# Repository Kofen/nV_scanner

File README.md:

# Nv scanner

FW is at best a hack

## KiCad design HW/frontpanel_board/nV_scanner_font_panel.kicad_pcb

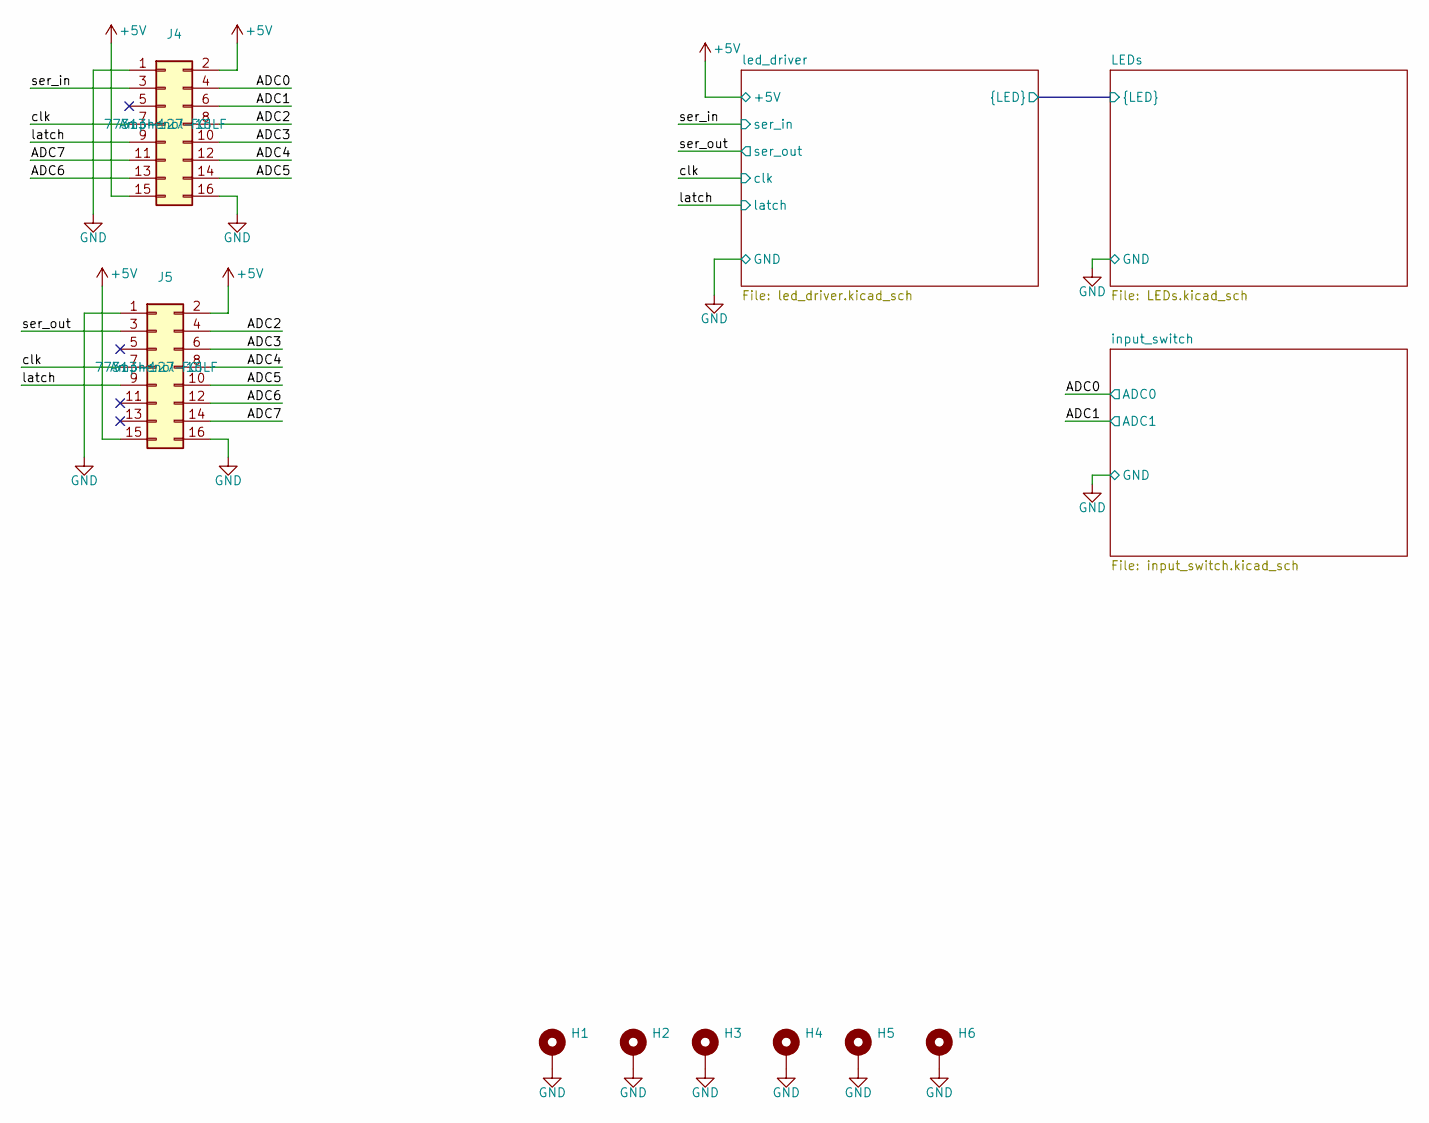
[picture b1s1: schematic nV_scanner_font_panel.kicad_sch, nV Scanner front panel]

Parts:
H1, H2, H3, H4, H5, H6: MountingHole_Pad; MountingHole_3.2mm_M3_solder_in_nut_reverse_8mm_mounting_he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
J4, J5: Conn_02x08_Odd_Even; PinHeader_2x08_P2.54mm_Vertical

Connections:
+5V: J4.2, J4.15, J5.2, J5.15; also elsewhere on the board
/ADC0: J4.4; also elsewhere on the board
/ADC1: J4.6; also elsewhere on the board
/ADC2: J4.8, J5.4
/ADC3: J4.10, J5.6
/ADC4: J4.12, J5.8
/ADC5: J4.14, J5.10
/ADC6: J4.13, J5.12
/ADC7: J4.11, J5.14
/clk: J4.7, J5.7; also elsewhere on the board
/latch: J4.9, J5.9; also elsewhere on the board
/ser_in: J4.3; also elsewhere on the board
/ser_out: J5.3; also elsewhere on the board
GND: H1.1, H2.1, H3.1, H4.1, H5.1, H6.1, J4.1, J4.16, J5.1, J5.16; also elsewhere on the board

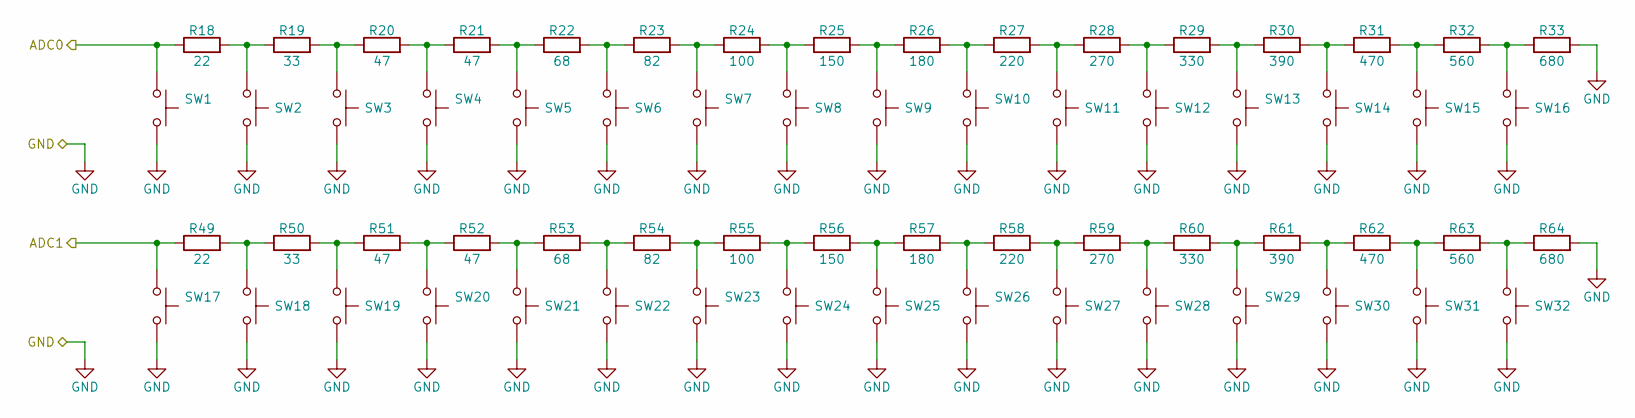
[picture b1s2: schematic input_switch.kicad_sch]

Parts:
R18, R49: 22; R_0603_1608Metric
R19, R50: 33; R_0603_1608Metric
R20, R21, R51, R52: 47; R_0603_1608Metric
R22, R53: 68; R_0603_1608Metric
R23, R54: 82; R_0603_1608Metric
R24, R55: 100; R_0603_1608Metric
R25, R56: 150; R_0603_1608Metric
R26, R57: 180; R_0603_1608Metric
R27, R58: 220; R_0603_1608Metric
R28, R59: 270; R_0603_1608Metric
R29, R60: 330; R_0603_1608Metric
R30, R61: 390; R_0603_1608Metric
R31, R62: 470; R_0603_1608Metric
R32, R63: 560; R_0603_1608Metric
R33, R64: 680; R_0603_1608Metric
SW1, SW2, SW3, SW4, SW5, SW6, SW7, SW8, SW9, SW10, SW11, SW12, SW13, SW14, SW15, SW16, SW17, SW18, SW19, SW20, SW21, SW22, SW23, SW24, SW25, SW26, SW27, SW28, SW29, SW30, SW31, SW32: SW_Push; SW_PUSH_6mm_H13mm

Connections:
/ADC0: R18.1, SW1.1; also elsewhere on the board
/ADC1: R49.1, SW17.1; also elsewhere on the board
GND: R33.2, R64.2, SW1.2, SW2.2, SW3.2, SW4.2, SW5.2, SW6.2, SW7.2, SW8.2, SW9.2, SW10.2, SW11.2, SW12.2, SW13.2, SW14.2, SW15.2, SW16.2, SW17.2, SW18.2, SW19.2, SW20.2, SW21.2, SW22.2, SW23.2, SW24.2, SW25.2, SW26.2, SW27.2, SW28.2, SW29.2, SW30.2, SW31.2, SW32.2; also elsewhere on the board
unnamed: R18.2, R19.1, SW2.1
unnamed: R19.2, R20.1, SW3.1
unnamed: R20.2, R21.1, SW4.1
unnamed: R21.2, R22.1, SW5.1
unnamed: R22.2, R23.1, SW6.1
unnamed: R23.2, R24.1, SW7.1
unnamed: R24.2, R25.1, SW8.1
unnamed: R25.2, R26.1, SW9.1
unnamed: R26.2, R27.1, SW10.1
unnamed: R27.2, R28.1, SW11.1
unnamed: R28.2, R29.1, SW12.1
unnamed: R29.2, R30.1, SW13.1
unnamed: R30.2, R31.1, SW14.1
unnamed: R31.2, R32.1, SW15.1
unnamed: R32.2, R33.1, SW16.1
unnamed: R49.2, R50.1, SW18.1
unnamed: R50.2, R51.1, SW19.1
unnamed: R51.2, R52.1, SW20.1
unnamed: R52.2, R53.1, SW21.1
unnamed: R53.2, R54.1, SW22.1
unnamed: R54.2, R55.1, SW23.1
unnamed: R55.2, R56.1, SW24.1
unnamed: R56.2, R57.1, SW25.1
unnamed: R57.2, R58.1, SW26.1
unnamed: R58.2, R59.1, SW27.1
unnamed: R59.2, R60.1, SW28.1
unnamed: R60.2, R61.1, SW29.1
unnamed: R61.2, R62.1, SW30.1
unnamed: R62.2, R63.1, SW31.1
unnamed: R63.2, R64.1, SW32.1

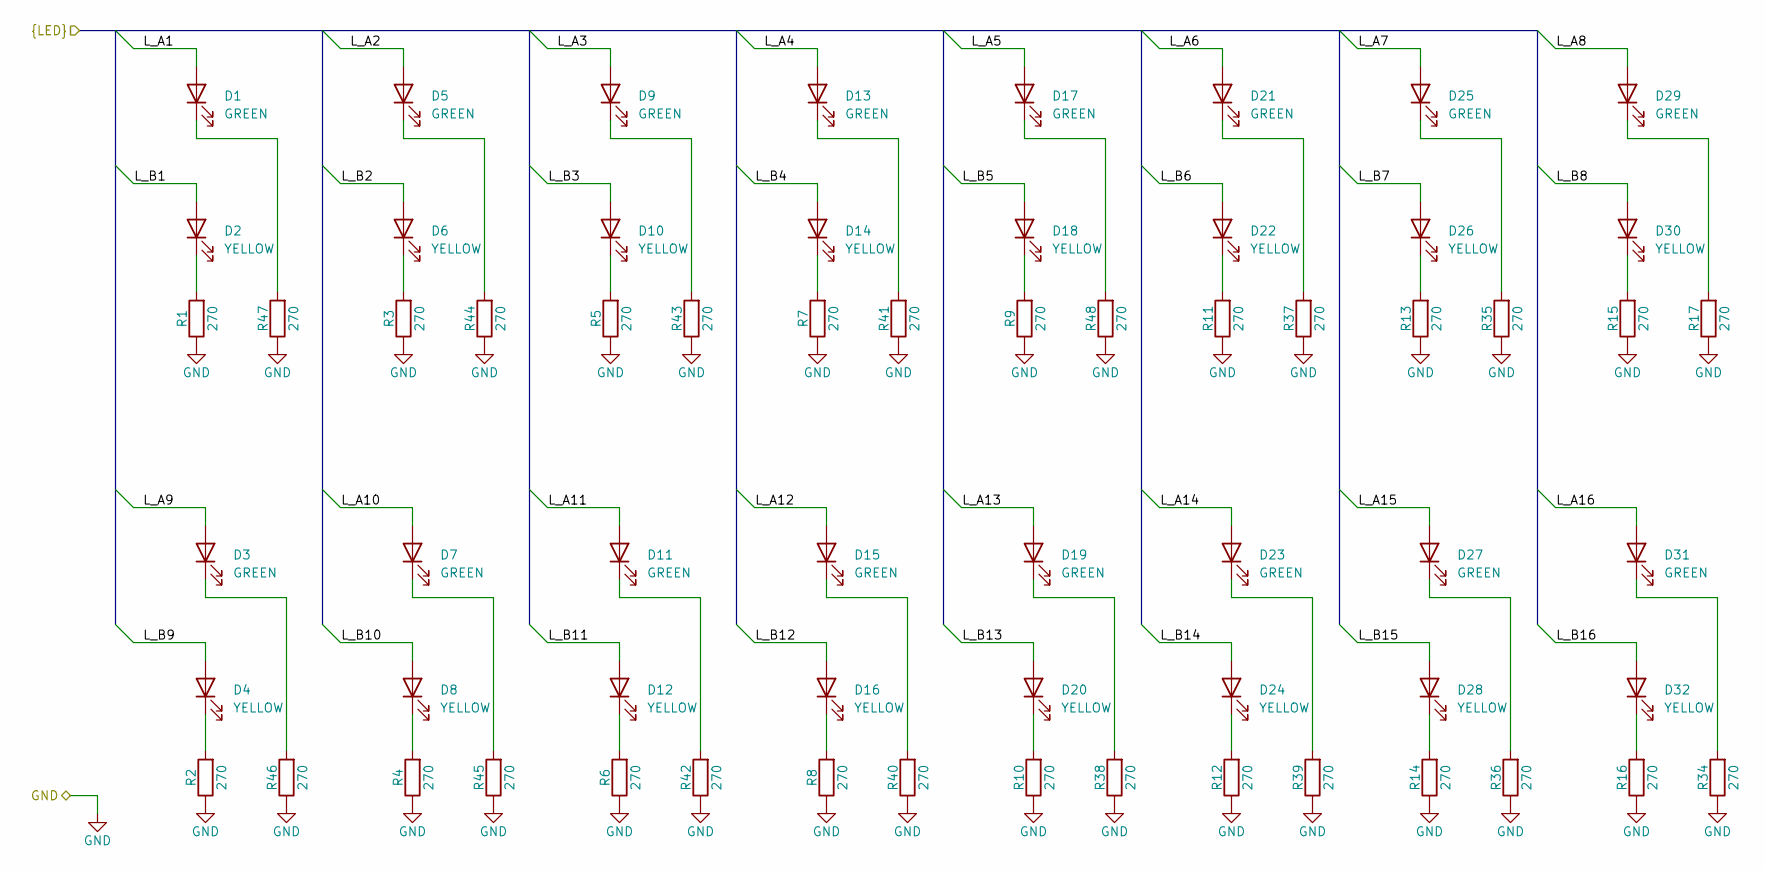
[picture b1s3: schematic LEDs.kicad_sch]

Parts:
D1, D3, D5, D7, D9, D11, D13, D15, D17, D19, D21, D23, D25, D27, D29, D31: GREEN; LED_D3.0mm_Clear
D2, D4, D6, D8, D10, D12, D14, D16, D18, D20, D22, D24, D26, D28, D30, D32: YELLOW; LED_D3.0mm_Clear
R1, R2, R3, R4, R5, R6, R7, R8, R9, R10, R11, R12, R13, R14, R15, R16, R17, R34, R35, R36, R37, R38, R39, R40, R41, R42, R43, R44, R45, R46, R47, R48: 270; R_0603_1608Metric

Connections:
/LEDs/L_A1: D1.2 (A); also elsewhere on the board
/LEDs/L_A2: D5.2 (A); also elsewhere on the board
/LEDs/L_A3: D9.2 (A); also elsewhere on the board
/LEDs/L_A4: D13.2 (A); also elsewhere on the board
/LEDs/L_A5: D17.2 (A); also elsewhere on the board
/LEDs/L_A6: D21.2 (A); also elsewhere on the board
/LEDs/L_A7: D25.2 (A); also elsewhere on the board
/LEDs/L_A8: D29.2 (A); also elsewhere on the board
/LEDs/L_A9: D3.2 (A); also elsewhere on the board
/LEDs/L_A10: D7.2 (A); also elsewhere on the board
/LEDs/L_A11: D11.2 (A); also elsewhere on the board
/LEDs/L_A12: D15.2 (A); also elsewhere on the board
/LEDs/L_A13: D19.2 (A); also elsewhere on the board
/LEDs/L_A14: D23.2 (A); also elsewhere on the board
/LEDs/L_A15: D27.2 (A); also elsewhere on the board
/LEDs/L_A16: D31.2 (A); also elsewhere on the board
/LEDs/L_B1: D2.2 (A); also elsewhere on the board
/LEDs/L_B2: D6.2 (A); also elsewhere on the board
/LEDs/L_B3: D10.2 (A); also elsewhere on the board
/LEDs/L_B4: D14.2 (A); also elsewhere on the board
/LEDs/L_B5: D18.2 (A); also elsewhere on the board
/LEDs/L_B6: D22.2 (A); also elsewhere on the board
/LEDs/L_B7: D26.2 (A); also elsewhere on the board
/LEDs/L_B8: D30.2 (A); also elsewhere on the board
/LEDs/L_B9: D4.2 (A); also elsewhere on the board
/LEDs/L_B10: D8.2 (A); also elsewhere on the board
/LEDs/L_B11: D12.2 (A); also elsewhere on the board
/LEDs/L_B12: D16.2 (A); also elsewhere on the board
/LEDs/L_B13: D20.2 (A); also elsewhere on the board
/LEDs/L_B14: D24.2 (A); also elsewhere on the board
/LEDs/L_B15: D28.2 (A); also elsewhere on the board
/LEDs/L_B16: D32.2 (A); also elsewhere on the board
GND: R1.1, R2.1, R3.1, R4.1, R5.1, R6.1, R7.1, R8.1, R9.1, R10.1, R11.1, R12.1, R13.1, R14.1, R15.1, R16.1, R17.1, R34.1, R35.1, R36.1, R37.1, R38.1, R39.1, R40.1, R41.1, R42.1, R43.1, R44.1, R45.1, R46.1, R47.1, R48.1; also elsewhere on the board
unnamed: D1.1 (K), R47.2
unnamed: D2.1 (K), R1.2
unnamed: D3.1 (K), R46.2
unnamed: D4.1 (K), R2.2
unnamed: D5.1 (K), R44.2
unnamed: D6.1 (K), R3.2
unnamed: D7.1 (K), R45.2
unnamed: D8.1 (K), R4.2
unnamed: D9.1 (K), R43.2
unnamed: D10.1 (K), R5.2
unnamed: D11.1 (K), R42.2
unnamed: D12.1 (K), R6.2
unnamed: D13.1 (K), R41.2
unnamed: D14.1 (K), R7.2
unnamed: D15.1 (K), R40.2
unnamed: D16.1 (K), R8.2
unnamed: D17.1 (K), R48.2
unnamed: D18.1 (K), R9.2
unnamed: D19.1 (K), R38.2
unnamed: D20.1 (K), R10.2
unnamed: D21.1 (K), R37.2
unnamed: D22.1 (K), R11.2
unnamed: D23.1 (K), R39.2
unnamed: D24.1 (K), R12.2
unnamed: D25.1 (K), R35.2
unnamed: D26.1 (K), R13.2
unnamed: D27.1 (K), R36.2
unnamed: D28.1 (K), R14.2
unnamed: D29.1 (K), R17.2
unnamed: D30.1 (K), R15.2
unnamed: D31.1 (K), R34.2
unnamed: D32.1 (K), R16.2

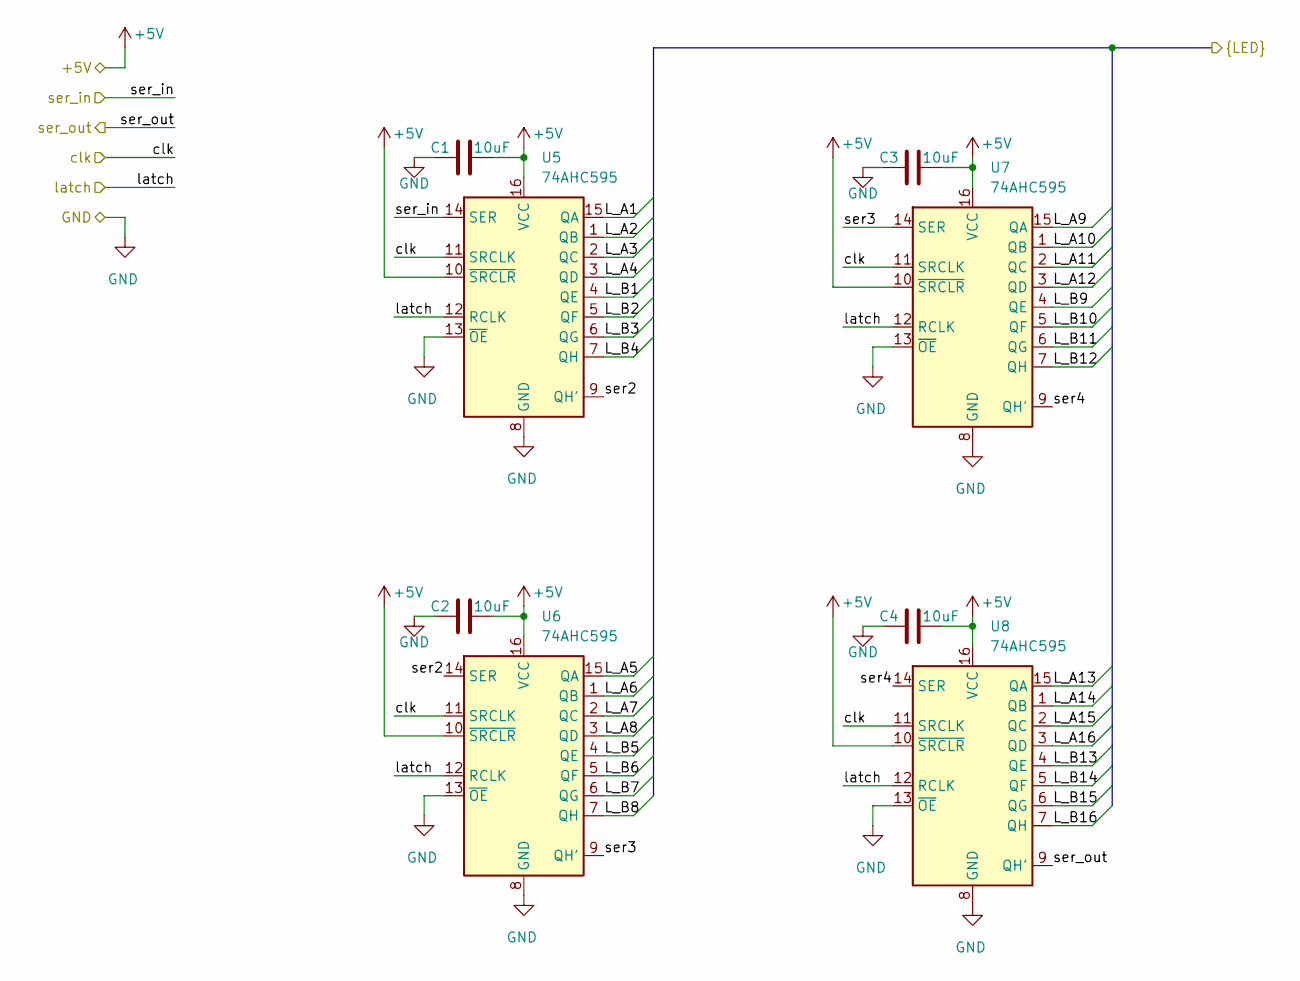
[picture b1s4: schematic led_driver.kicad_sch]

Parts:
C1, C2, C3, C4: 10uF; C_0603_1608Metric
U5, U6, U7, U8: 74AHC595; SOIC-16_3.9x9.9mm_P1.27mm

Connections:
+5V: C1.2, C2.2, C3.2, C4.2, U5.10 (~SRCLR), U5.16 (VCC), U6.10 (~SRCLR), U6.16 (VCC), U7.10 (~SRCLR), U7.16 (VCC), U8.10 (~SRCLR), U8.16 (VCC); also elsewhere on the board
/LEDs/L_A1: U5.15 (QA); also elsewhere on the board
/LEDs/L_A2: U5.1 (QB); also elsewhere on the board
/LEDs/L_A3: U5.2 (QC); also elsewhere on the board
/LEDs/L_A4: U5.3 (QD); also elsewhere on the board
/LEDs/L_A5: U6.15 (QA); also elsewhere on the board
/LEDs/L_A6: U6.1 (QB); also elsewhere on the board
/LEDs/L_A7: U6.2 (QC); also elsewhere on the board
/LEDs/L_A8: U6.3 (QD); also elsewhere on the board
/LEDs/L_A9: U7.15 (QA); also elsewhere on the board
/LEDs/L_A10: U7.1 (QB); also elsewhere on the board
/LEDs/L_A11: U7.2 (QC); also elsewhere on the board
/LEDs/L_A12: U7.3 (QD); also elsewhere on the board
/LEDs/L_A13: U8.15 (QA); also elsewhere on the board
/LEDs/L_A14: U8.1 (QB); also elsewhere on the board
/LEDs/L_A15: U8.2 (QC); also elsewhere on the board
/LEDs/L_A16: U8.3 (QD); also elsewhere on the board
/LEDs/L_B1: U5.4 (QE); also elsewhere on the board
/LEDs/L_B2: U5.5 (QF); also elsewhere on the board
/LEDs/L_B3: U5.6 (QG); also elsewhere on the board
/LEDs/L_B4: U5.7 (QH); also elsewhere on the board
/LEDs/L_B5: U6.4 (QE); also elsewhere on the board
/LEDs/L_B6: U6.5 (QF); also elsewhere on the board
/LEDs/L_B7: U6.6 (QG); also elsewhere on the board
/LEDs/L_B8: U6.7 (QH); also elsewhere on the board
/LEDs/L_B9: U7.4 (QE); also elsewhere on the board
/LEDs/L_B10: U7.5 (QF); also elsewhere on the board
/LEDs/L_B11: U7.6 (QG); also elsewhere on the board
/LEDs/L_B12: U7.7 (QH); also elsewhere on the board
/LEDs/L_B13: U8.4 (QE); also elsewhere on the board
/LEDs/L_B14: U8.5 (QF); also elsewhere on the board
/LEDs/L_B15: U8.6 (QG); also elsewhere on the board
/LEDs/L_B16: U8.7 (QH); also elsewhere on the board
/clk: U5.11 (SRCLK), U6.11 (SRCLK), U7.11 (SRCLK), U8.11 (SRCLK); also elsewhere on the board
/latch: U5.12 (RCLK), U6.12 (RCLK), U7.12 (RCLK), U8.12 (RCLK); also elsewhere on the board
/led_driver/ser2: U5.9 (QH'), U6.14 (SER)
/led_driver/ser3: U6.9 (QH'), U7.14 (SER)
/led_driver/ser4: U7.9 (QH'), U8.14 (SER)
/ser_in: U5.14 (SER); also elsewhere on the board
/ser_out: U8.9 (QH'); also elsewhere on the board
GND: C1.1, C2.1, C3.1, C4.1, U5.8 (GND), U5.13 (~OE), U6.8 (GND), U6.13 (~OE), U7.8 (GND), U7.13 (~OE), U8.8 (GND), U8.13 (~OE); also elsewhere on the board

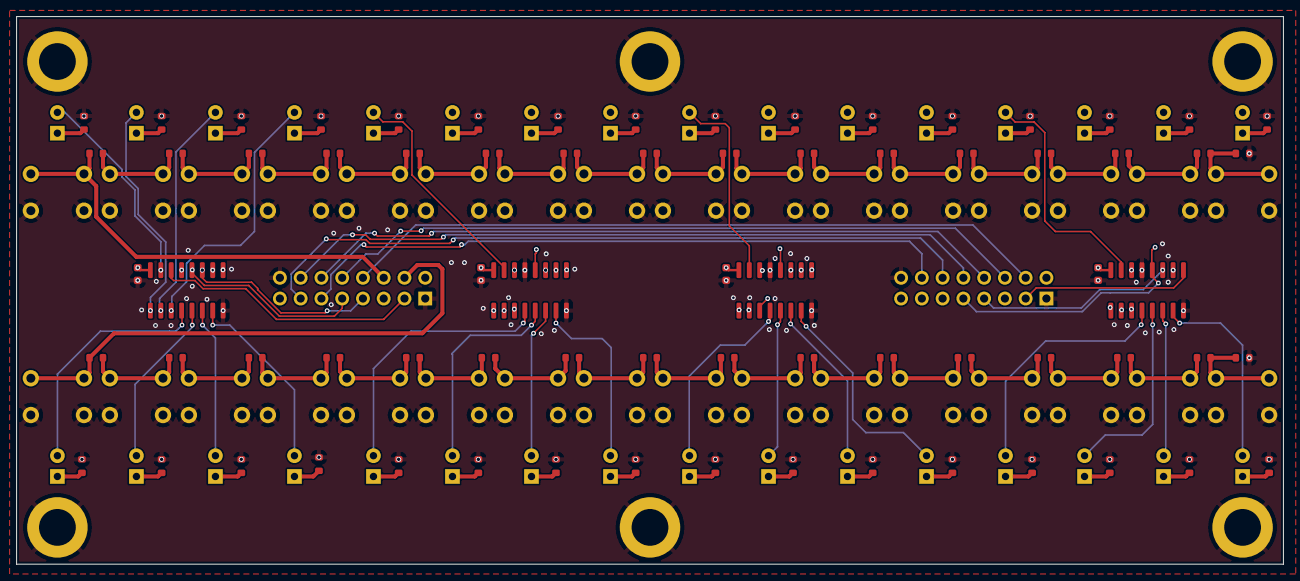
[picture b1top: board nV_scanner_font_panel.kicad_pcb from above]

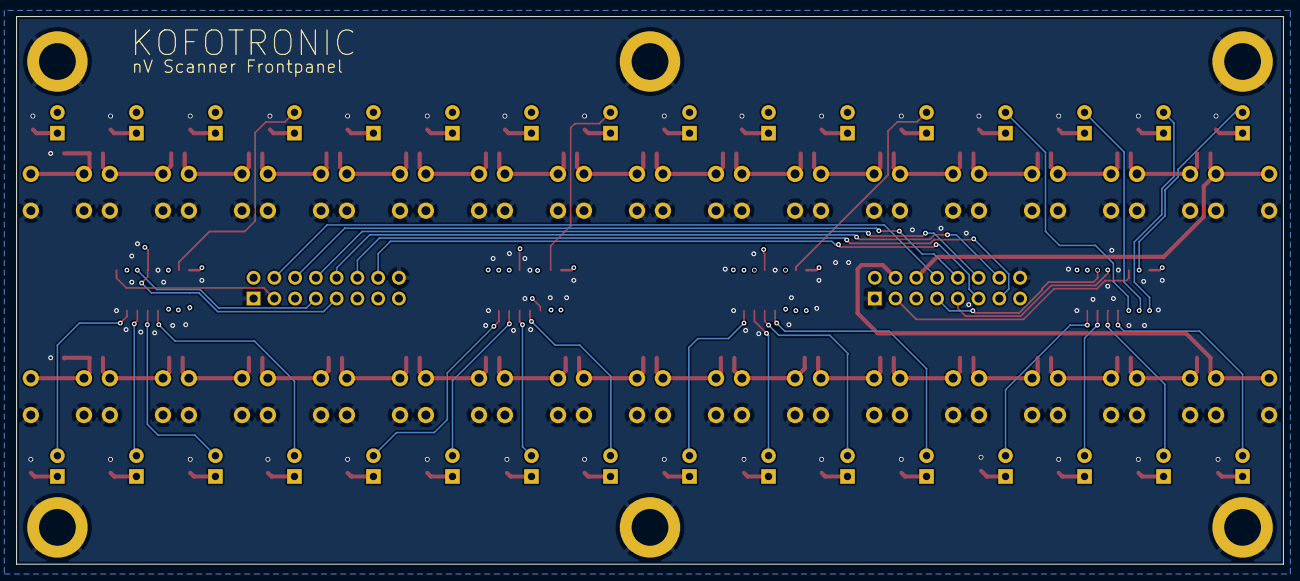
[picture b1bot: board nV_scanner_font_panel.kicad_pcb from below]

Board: 6 copper layers, 155.0 x 67.0 mm, 144 parts (8 on the bottom side), 111 nets.

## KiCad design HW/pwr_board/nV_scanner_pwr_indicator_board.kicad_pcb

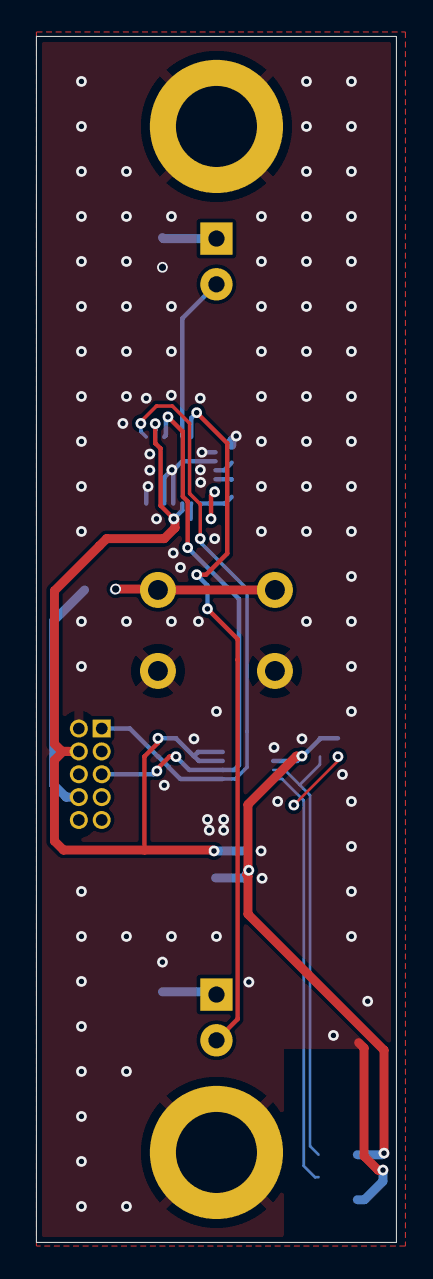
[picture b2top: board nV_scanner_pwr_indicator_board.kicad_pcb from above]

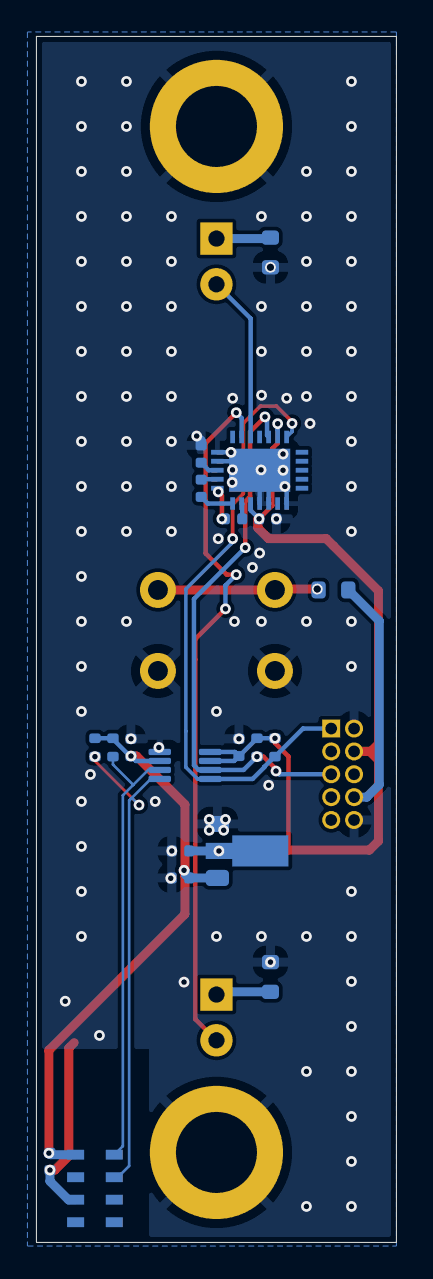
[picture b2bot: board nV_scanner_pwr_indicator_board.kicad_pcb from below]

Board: 4 copper layers, 20.0 x 67.0 mm, 26 parts (23 on the bottom side), 18 nets.

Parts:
C1, C2, C16, C17, C18, C19, C20, C21, C22: 10µ; C_0402_1005Metric
D1: GREEN; LED_D3.0mm_Clear
D2: YELLOW; LED_D3.0mm_Clear
H1, H2: MountingHole_Pad; MountingHole_3.2mm_M3_solder_in_nut_reverse_8mm_mounting_he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
J4: UPDI Debug Connector; PinHeader_2x05_P1.27mm_Vertical
R1, R47: 270; R_0603_1608Metric
R2: 470; R_0603_1608Metric
R6, R7, R8, R9: 4.7k; R_0402_1005Metric
SW1: SW_Push; SW_PUSH_6mm_H13mm
U1: MS8607; LGA-8_3x5mm_P1.25mm
U2: LP5521; NJA0024A
U5: PCA9306DC; VSSOP-8_2.3x2mm_P0.5mm
U11: AZ1117-3.3_SOT89; SOT-89-3

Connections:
+3.3V: C2.1, C16.1, C17.1, R8.2, R9.2, U1.1 (VDD), U5.2 (VREF1), U11.3 (VO)
+5V: C1.1, C18.1, C22.2, J4.4, R6.2, R7.2, U2.3 (VDD), U2.14 (EN), U5.7 (VREF2), U5.8 (EN), U11.2 (VI)
/PB4: J4.8, R2.2
/SCL: J4.5, R7.1, U2.15 (SCL), U5.6 (SCL2)
/SCL_3v3: R9.1, U1.8 (SCLK), U5.3 (SCL1)
/SDA: J4.1, R6.1, U2.13 (SDA), U5.5 (SDA2)
/SDA_3v3: R8.1, U1.7 (SDI/SDA), U5.4 (SDA1)
GND: C1.2, C2.2, C16.2, C17.2, C18.2, C21.2, C22.1, H1.1, H2.1, J4.2, J4.10, R1.1, R47.1, SW1.2, U1.3 (GND), U2.4 (GND), U2.5 (CLK_32K), U2.7 (TRIG), U2.20 (ADDR0), U2.21 (ADDR1), U2.25 (GND), U5.1 (GND), U11.1 (GND)
unnamed: D1.2 (A), U2.17 (R)
unnamed: D1.1 (K), R47.2
unnamed: D2.2 (A), U2.18 (G)
unnamed: D2.1 (K), R1.2
unnamed: R2.1, SW1.1
unnamed: C19.1, U2.24 (CFLY1N)
unnamed: C19.2, U2.2 (CFLY1P)
unnamed: C20.1, U2.23 (CFLY2N)
unnamed: C20.2, U2.1 (CFLY2P)
unnamed: C21.1, U2.22 (VOUT)

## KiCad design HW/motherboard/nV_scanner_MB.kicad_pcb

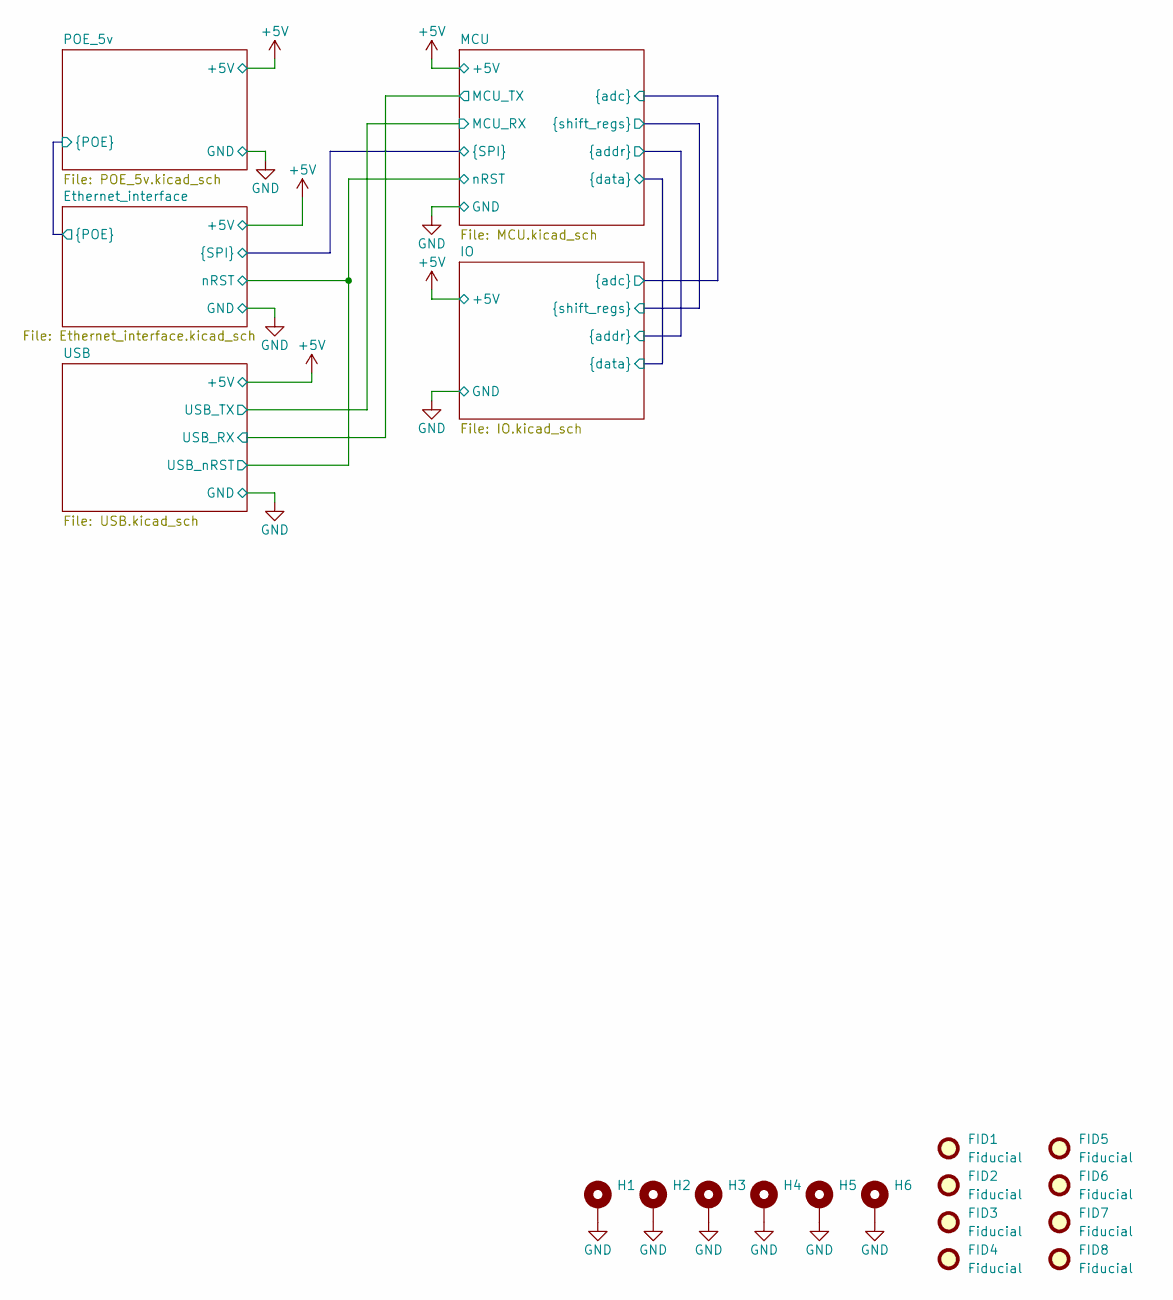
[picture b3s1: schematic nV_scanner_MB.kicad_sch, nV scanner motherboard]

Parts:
FID1, FID2, FID3, FID4, FID5, FID6, FID7, FID8: Fiducial; Fiducial_0.75mm_Mask1.5mm
H1, H2, H3, H4, H5, H6: MountingHole_Pad; MountingHole_3.2mm_M3_solder_in_nut_reverse_mount_4mm_space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

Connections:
GND: H1.1, H2.1, H3.1, H4.1, H5.1, H6.1; also elsewhere on the board

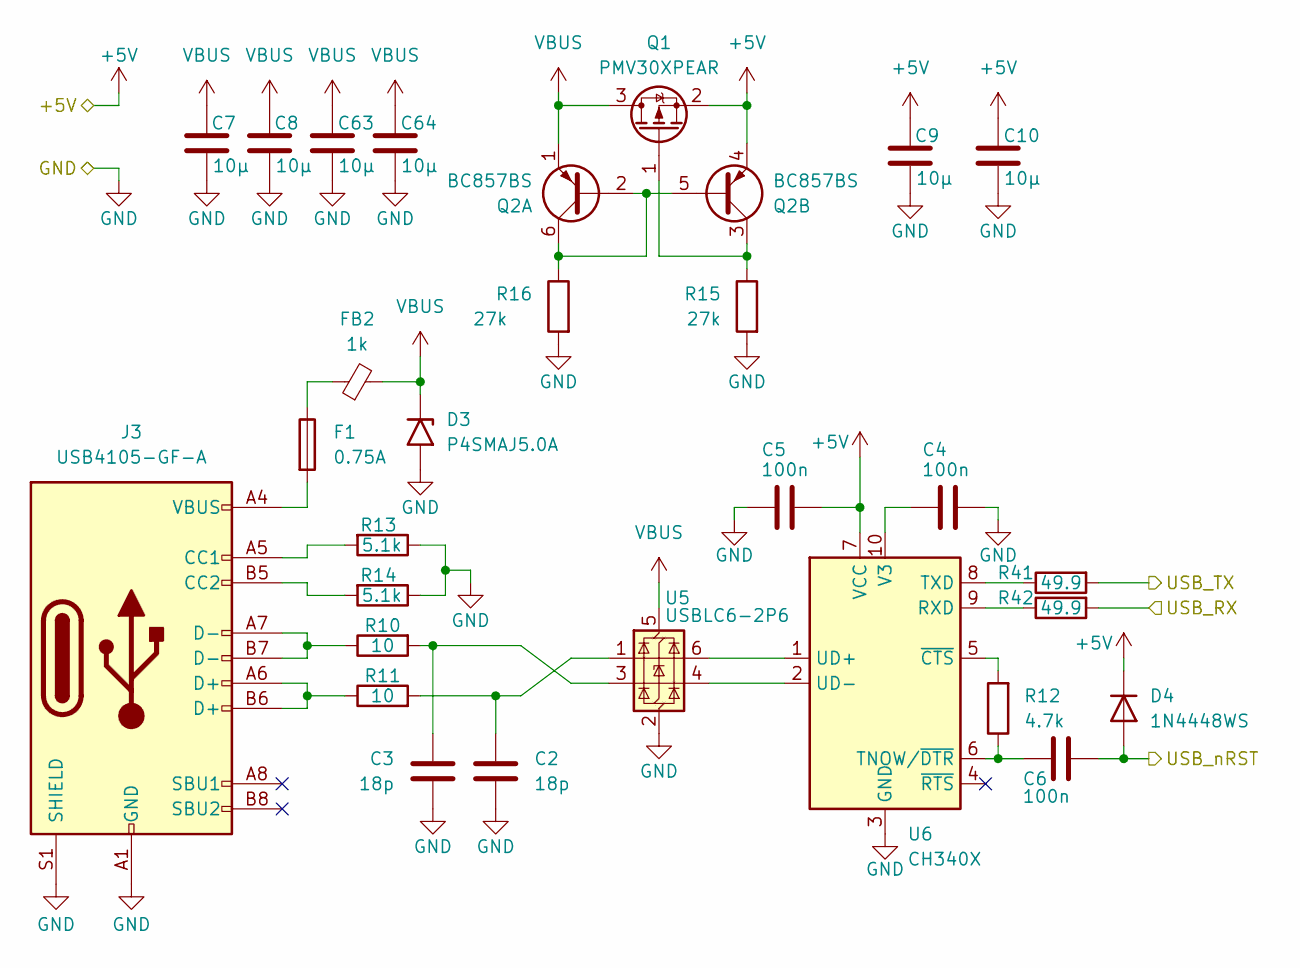
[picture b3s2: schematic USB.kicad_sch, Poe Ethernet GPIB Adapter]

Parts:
C2, C3: 18p; C_0402_1005Metric; JLCPCB C1549
C4, C5, C6: 100n; C_0402_1005Metric; JLCPCB C1525
C7, C8, C9, C10, C63, C64: 10µ; C_0402_1005Metric; JLCPCB C15525
D3: P4SMAJ5.0A; D_SMA; JLCPCB C391580
D4: 1N4448WS; D_SOD-323; JLCPCB C8602
F1: 0.75A; Fuse_1812_4532Metric; JLCPCB C3107
FB2: 1k; L_0805_2012Metric; JLCPCB C710395
J3: USB4105-GF-A; USB_C_Receptacle_GCT_USB4105-xx-A_16P_TopMnt_Horizontal; JLCPCB C3020560
Q1: PMV30XPEAR; SOT-23
Q2: BC857BS; SOT-363_SC-70-6
R10, R11: 10; R_0402_1005Metric
R12: 4.7k; R_0402_1005Metric
R13, R14: 5.1k; R_0402_1005Metric
R15, R16: 27k; R_0402_1005Metric
R41, R42: 49.9; R_0402_1005Metric
U5: USBLC6-2P6; SOT-666; JLCPCB C2827693
U6: CH340X; MSOP-10_3x3mm_P0.5mm; JLCPCB C3035748

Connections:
+5V: C5.2, C9.1, C10.1, D4.1 (K), Q1.2 (S), Q2.4 (E2), U6.7 (VCC); also elsewhere on the board
/Ethernet_interface/nRST: C6.2, D4.2 (A); also elsewhere on the board
/MCU/MCU_RX: R41.2; also elsewhere on the board
/MCU/MCU_TX: R42.2; also elsewhere on the board
GND: C2.2, C3.2, C4.2, C5.1, C7.2, C8.2, C9.2, C10.2, C63.2, C64.2, D3.2 (A2), J3.A1 (GND), J3.A12 (GND), J3.B1 (GND), J3.B12 (GND), J3.S1 (SHIELD), R13.1, R14.1, R15.2, R16.2, U5.2 (GND), U6.3 (GND); also elsewhere on the board
unnamed: C2.1, R11.2, U5.1 (I/O1)
unnamed: C3.1, R10.2, U5.3 (I/O2)
unnamed: F1.1, FB2.1
unnamed: F1.2, J3.A4 (VBUS), J3.A9 (VBUS), J3.B4 (VBUS), J3.B9 (VBUS)
unnamed: J3.A5 (CC1), R13.2
unnamed: J3.B5 (CC2), R14.2
unnamed: J3.A6 (D+), J3.B6 (D+), R11.1
unnamed: J3.A7 (D-), J3.B7 (D-), R10.1
unnamed: Q1.1 (G), Q2.3 (C2), R15.1
unnamed: Q2.2 (B1), Q2.5 (B2), Q2.6 (C1), R16.1
unnamed: R42.1, U6.9 (RXD)
unnamed: C6.1, R12.1, U6.6 (TNOW/~DTR)
unnamed: R41.1, U6.8 (TXD)
unnamed: U5.6 (I/O1), U6.1 (UD+)
unnamed: U5.4 (I/O2), U6.2 (UD-)
unnamed: C4.1, U6.10 (V3)
unnamed: R12.2, U6.5 (~CTS)
VBUS: C7.1, C8.1, C63.1, C64.1, D3.1 (A1), FB2.2, Q1.3 (D), Q2.1 (E1), U5.5 (VBUS)

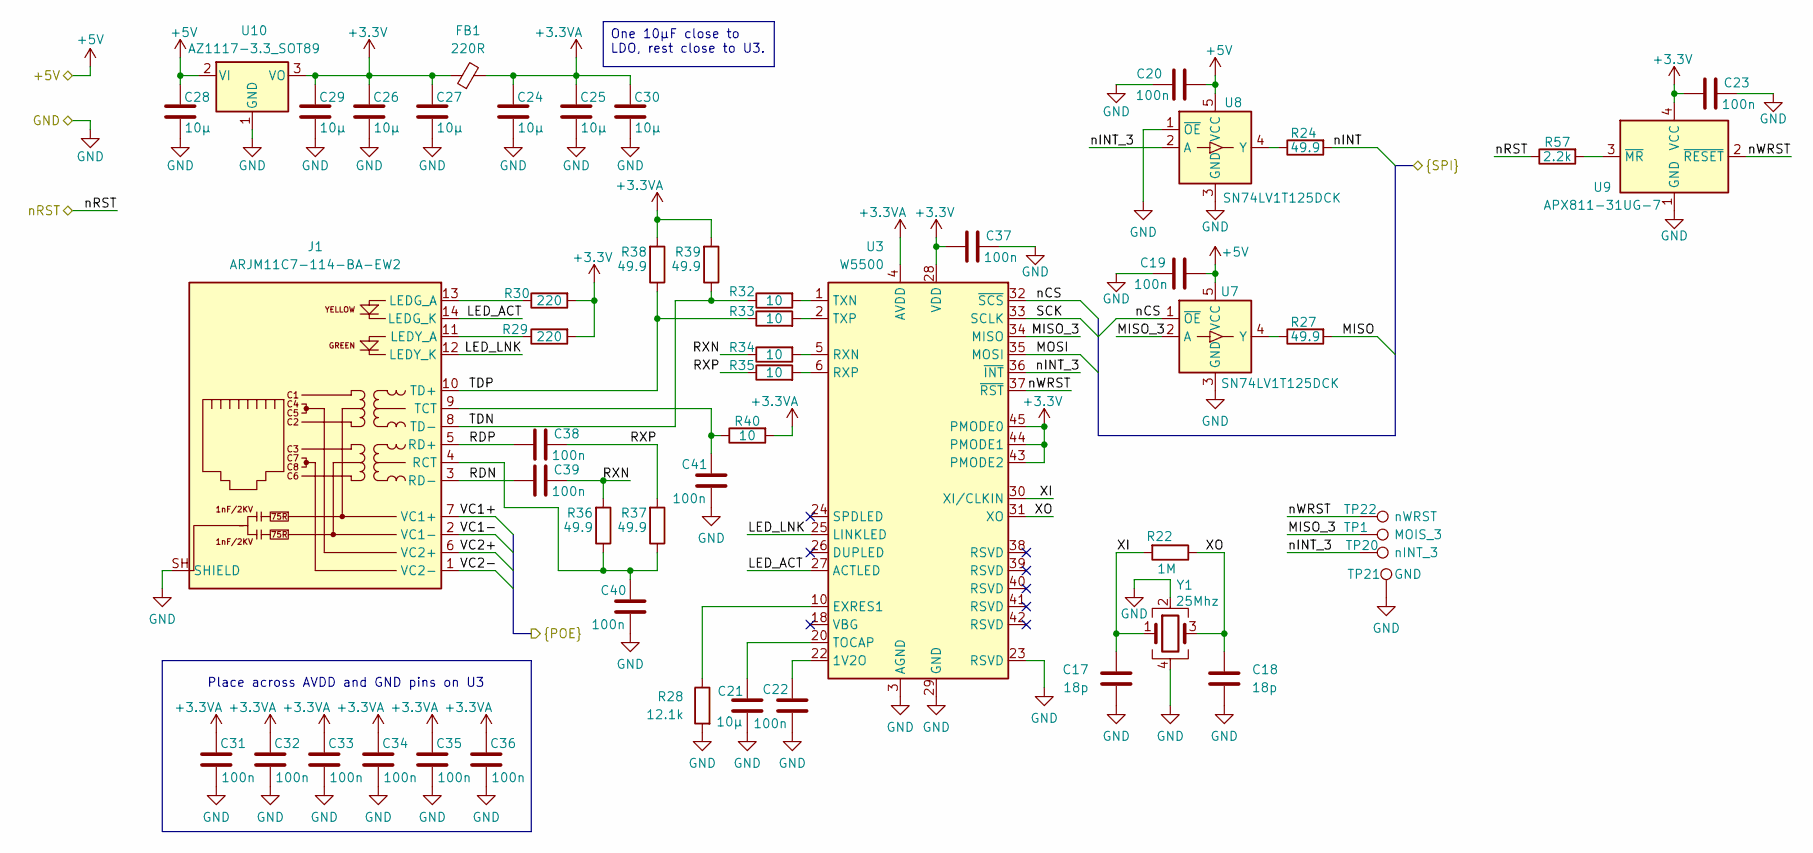
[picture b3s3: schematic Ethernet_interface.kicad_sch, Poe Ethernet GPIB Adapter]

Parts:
C17, C18: 18p; C_0402_1005Metric; JLCPCB C1549
C19, C20, C22, C23, C31, C32, C33, C34, C35, C36, C37, C38, C39, C40, C41: 100n; C_0402_1005Metric; JLCPCB C1525
C21, C24, C25, C26, C27, C28, C29, C30: 10µ; C_0402_1005Metric; JLCPCB C15525
FB1: 220R; L_0603_1608Metric; JLCPCB C139471
J1: ARJM11C7-114-BA-EW2; RJ45_ARJM11C7-114-BA-EW2
R22: 1M; R_0402_1005Metric
R24, R27, R36, R37, R38, R39: 49.9; R_0402_1005Metric
R28: 12.1k; R_0402_1005Metric
R29, R30: 220; R_0402_1005Metric
R32, R33, R34, R35, R40: 10; R_0402_1005Metric
R57: 2.2k; R_0402_1005Metric
TP1: MOIS_3; TestPoint_Pad_D1.0mm
TP20: nINT_3; TestPoint_Pad_D1.0mm
TP21: GND; TestPoint_Pad_D1.0mm
TP22: nWRST; TestPoint_Pad_D1.0mm
U3: W5500; LQFP-48_7x7mm_P0.5mm; JLCPCB C32843
U7, U8: SN74LV1T125DCK; SOT-353_SC-70-5; JLCPCB C2859742
U9: APX811-31UG-7; SOT-143; JLCPCB C150481
U10: AZ1117-3.3_SOT89; SOT-89-3; JLCPCB C362111
Y1: 25Mhz; Crystal_SMD_2520-4Pin_2.5x2.0mm; JLCPCB C5727305

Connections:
+3.3V: C23.2, C26.1, C27.1, C29.1, C37.2, FB1.1, R29.2, R30.2, U3.28 (VDD), U3.43 (PMODE2), U3.44 (PMODE1), U3.45 (PMODE0), U9.4 (VCC), U10.3 (VO)
+3.3VA: C24.1, C25.1, C30.1, C31.2, C32.2, C33.2, C34.2, C35.2, C36.2, FB1.2, R38.2, R39.2, R40.2, U3.4 (AVDD), U3.8 (AVDD), U3.11 (AVDD), U3.15 (AVDD), U3.17 (AVDD), U3.21 (AVDD)
+5V: C19.2, C20.2, C28.1, U7.5 (VCC), U8.5 (VCC), U10.2 (VI); also elsewhere on the board
/Ethernet_interface/LED_ACT: J1.14 (LEDG_K), U3.27 (ACTLED)
/Ethernet_interface/LED_LNK: J1.12 (LEDY_K), U3.25 (LINKLED)
/Ethernet_interface/MISO: R27.2; also elsewhere on the board
/Ethernet_interface/MISO_3: TP1.1, U3.34 (MISO), U7.2 (A)
/Ethernet_interface/MOSI: U3.35 (MOSI); also elsewhere on the board
/Ethernet_interface/RDN: C39.2, J1.3 (RD-)
/Ethernet_interface/RDP: C38.2, J1.5 (RD+)
/Ethernet_interface/RXN: C39.1, R34.1, R36.2
/Ethernet_interface/RXP: C38.1, R35.1, R37.2
/Ethernet_interface/SCK: U3.33 (SCLK); also elsewhere on the board
/Ethernet_interface/TDN: J1.8 (TD-), R32.1, R39.1
/Ethernet_interface/TDP: J1.10 (TD+), R33.1, R38.1
/Ethernet_interface/VC1+: J1.7 (VC1+); also elsewhere on the board
/Ethernet_interface/VC1-: J1.2 (VC1-); also elsewhere on the board
/Ethernet_interface/VC2+: J1.6 (VC2+); also elsewhere on the board
/Ethernet_interface/VC2-: J1.1 (VC2-); also elsewhere on the board
/Ethernet_interface/XI: C17.1, R22.2, U3.30 (XI/CLKIN), Y1.1
/Ethernet_interface/XO: C18.1, R22.1, U3.31 (XO), Y1.3
/Ethernet_interface/nCS: U3.32 (~SCS), U7.1 (~OE); also elsewhere on the board
/Ethernet_interface/nINT: R24.2; also elsewhere on the board
/Ethernet_interface/nINT_3: TP20.1, U3.36 (~INT), U8.2 (A)
/Ethernet_interface/nRST: R57.1; also elsewhere on the board
/Ethernet_interface/nWRST: TP22.1, U3.37 (~RST), U9.2 (~RESET)
GND: C17.2, C18.2, C19.1, C20.1, C21.2, C22.1, C23.1, C24.2, C25.2, C26.2, C27.2, C28.2, C29.2, C30.2, C31.1, C32.1, C33.1, C34.1, C35.1, C36.1, C37.1, C40.1, C41.1, J1.SH (SHIELD), R28.2, TP21.1, U3.3 (AGND), U3.9 (AGND), U3.14 (AGND), U3.16 (AGND), U3.19 (AGND), U3.23 (RSVD), U3.29 (GND), U3.48 (AGND), U7.3 (GND), U8.1 (~OE), U8.3 (GND), U9.1 (GND), U10.1 (GND), Y1.2, Y1.4; also elsewhere on the board
unnamed: J1.13 (LEDG_A), R30.1
unnamed: J1.11 (LEDY_A), R29.1
unnamed: C40.2, J1.4 (RCT), R36.1, R37.1
unnamed: C41.2, J1.9 (TCT), R40.1
unnamed: C22.2, U3.22 (1V2O)
unnamed: R28.1, U3.10 (EXRES1)
unnamed: R34.2, U3.5 (RXN)
unnamed: R35.2, U3.6 (RXP)
unnamed: C21.1, U3.20 (TOCAP)
unnamed: R32.2, U3.1 (TXN)
unnamed: R33.2, U3.2 (TXP)
unnamed: R27.1, U7.4 (Y)
unnamed: R24.1, U8.4 (Y)
unnamed: R57.2, U9.3 (~MR)

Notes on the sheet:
Place across AVDD and GND pins on U3
One 10µF close to LDO, rest close to U3.
